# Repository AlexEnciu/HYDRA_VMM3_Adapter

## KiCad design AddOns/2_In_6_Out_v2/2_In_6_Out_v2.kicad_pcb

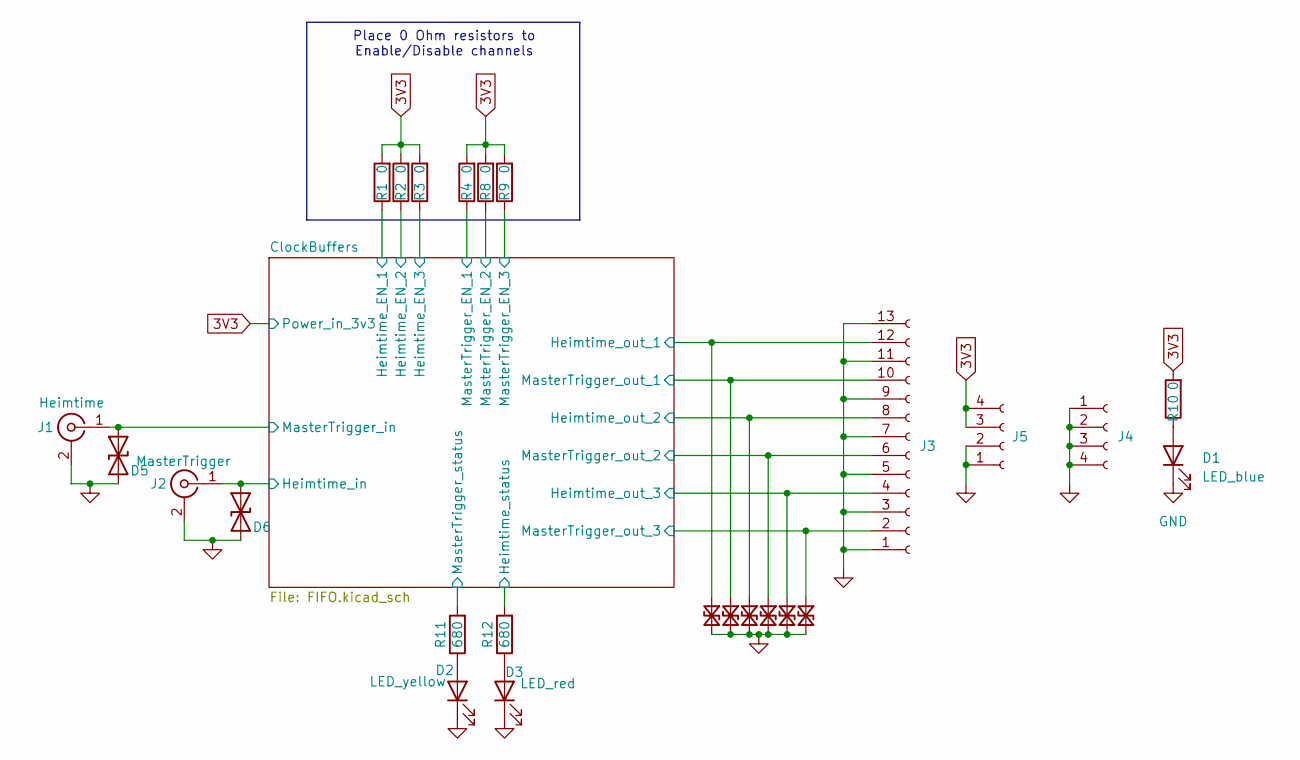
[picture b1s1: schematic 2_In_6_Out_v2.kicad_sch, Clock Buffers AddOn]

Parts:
D1: LED_blue; LED_0603_1608Metric
D2: LED_yellow; LED_0603_1608Metric
D3: LED_red; LED_0603_1608Metric
D5, D6, D7, D8, D9, D10, D11, D13: SP1333-01UTG; D_0201_0603Metric
J1: Heimtime; LINX_CONMCX002-SMD-T
J2: MasterTrigger; LINX_CONMCX002-SMD-T
J3: Conn_01x13_Socket; PinHeader_1x13_P1.27mm_Vertical
J4, J5: Conn_01x04_Socket; PinHeader_1x04_P1.27mm_Vertical
R1, R2, R3, R4, R8, R9: 0; R_0402_1005Metric
R10: 0; R_0603_1608Metric
R11, R12: 680; R_0402_1005Metric

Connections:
3V3: J5.3, J5.4, R1.2, R2.2, R3.2, R4.2, R8.2, R9.2, R10.2; also elsewhere on the board
/ClockBuffers/Heimtime_EN_1: R1.1; also elsewhere on the board
/ClockBuffers/Heimtime_EN_2: R2.1; also elsewhere on the board
/ClockBuffers/Heimtime_EN_3: R3.1; also elsewhere on the board
/ClockBuffers/Heimtime_in: D6.1 (A1), J2.1 (In); also elsewhere on the board
/ClockBuffers/Heimtime_out_1: D13.1 (A1), J3.12; also elsewhere on the board
/ClockBuffers/Heimtime_out_2: D8.1 (A1), J3.8; also elsewhere on the board
/ClockBuffers/Heimtime_out_3: D10.1 (A1), J3.4; also elsewhere on the board
/ClockBuffers/Heimtime_status: R12.2; also elsewhere on the board
/ClockBuffers/MasterTrigger_EN_1: R4.1; also elsewhere on the board
/ClockBuffers/MasterTrigger_EN_2: R8.1; also elsewhere on the board
/ClockBuffers/MasterTrigger_EN_3: R9.1; also elsewhere on the board
/ClockBuffers/MasterTrigger_in: D5.1 (A1), J1.1 (In); also elsewhere on the board
/ClockBuffers/MasterTrigger_out_1: D7.1 (A1), J3.10; also elsewhere on the board
/ClockBuffers/MasterTrigger_out_2: D9.1 (A1), J3.6; also elsewhere on the board
/ClockBuffers/MasterTrigger_out_3: D11.1 (A1), J3.2; also elsewhere on the board
/ClockBuffers/MasterTrigger_status: R11.2; also elsewhere on the board
GND: D1.1 (K), D2.1 (K), D3.1 (K), D5.2 (A2), D6.2 (A2), D7.2 (A2), D8.2 (A2), D9.2 (A2), D10.2 (A2), D11.2 (A2), D13.2 (A2), J1.2 (Ext), J2.2 (Ext), J3.1, J3.3, J3.5, J3.7, J3.9, J3.11, J3.13, J4.1, J4.2, J4.3, J4.4, J5.1, J5.2; also elsewhere on the board
unnamed: D1.2 (A), R10.1
unnamed: D2.2 (A), R11.1
unnamed: D3.2 (A), R12.1

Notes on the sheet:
Place 0 Ohm resistors to Enable/Disable channels

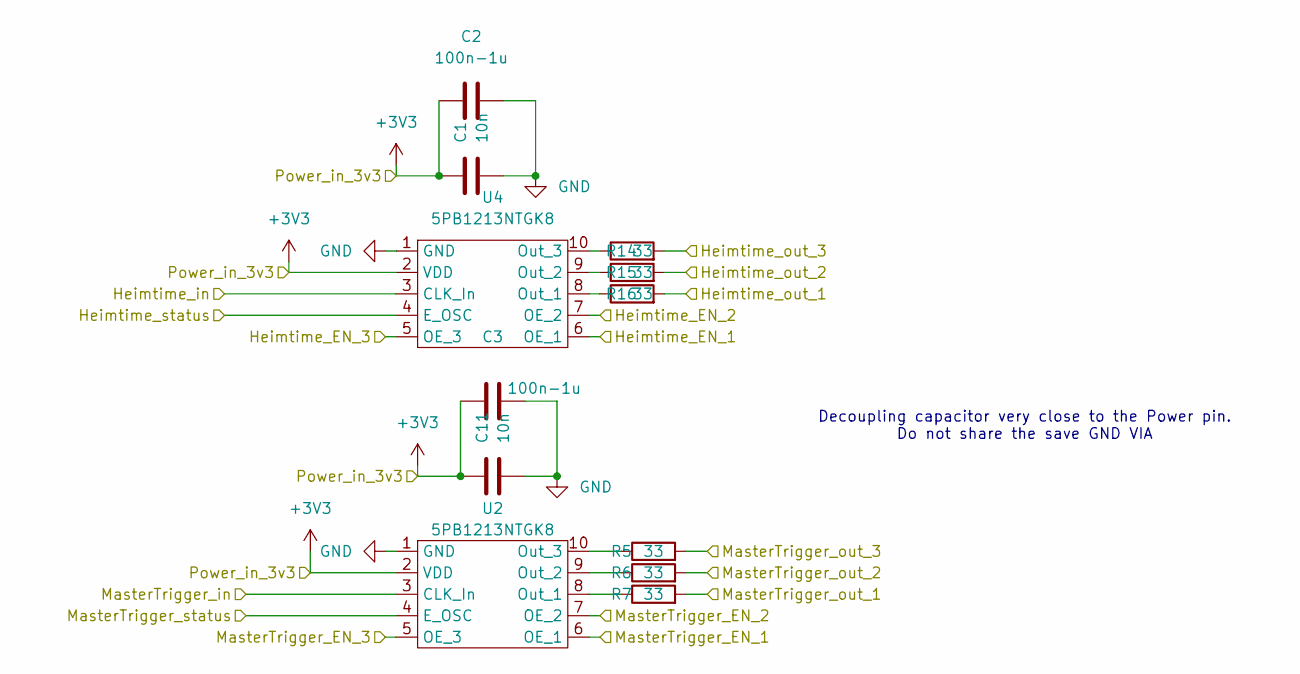
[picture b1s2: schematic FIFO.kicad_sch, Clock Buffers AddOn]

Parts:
C1, C11: 10n; C_0402_1005Metric
C2, C3: 100n-1u; C_0402_1005Metric
R5, R6, R7, R14, R15, R16: 33; R_0402_1005Metric
U2, U4: 5PB1213NTGK8

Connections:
3V3: C1.1, C2.1, C3.1, C11.1, U2.2 (VDD), U4.2 (VDD); also elsewhere on the board
/ClockBuffers/Heimtime_EN_1: U4.6 (OE_1); also elsewhere on the board
/ClockBuffers/Heimtime_EN_2: U4.7 (OE_2); also elsewhere on the board
/ClockBuffers/Heimtime_EN_3: U4.5 (OE_3); also elsewhere on the board
/ClockBuffers/Heimtime_in: U4.3 (CLK_In); also elsewhere on the board
/ClockBuffers/Heimtime_out_1: R16.2; also elsewhere on the board
/ClockBuffers/Heimtime_out_2: R15.2; also elsewhere on the board
/ClockBuffers/Heimtime_out_3: R14.2; also elsewhere on the board
/ClockBuffers/Heimtime_status: U4.4 (E_OSC); also elsewhere on the board
/ClockBuffers/MasterTrigger_EN_1: U2.6 (OE_1); also elsewhere on the board
/ClockBuffers/MasterTrigger_EN_2: U2.7 (OE_2); also elsewhere on the board
/ClockBuffers/MasterTrigger_EN_3: U2.5 (OE_3); also elsewhere on the board
/ClockBuffers/MasterTrigger_in: U2.3 (CLK_In); also elsewhere on the board
/ClockBuffers/MasterTrigger_out_1: R7.2; also elsewhere on the board
/ClockBuffers/MasterTrigger_out_2: R6.2; also elsewhere on the board
/ClockBuffers/MasterTrigger_out_3: R5.2; also elsewhere on the board
/ClockBuffers/MasterTrigger_status: U2.4 (E_OSC); also elsewhere on the board
GND: C1.2, C2.2, C3.2, C11.2, U2.1 (GND), U4.1 (GND); also elsewhere on the board
unnamed: R7.1, U2.8 (Out_1)
unnamed: R6.1, U2.9 (Out_2)
unnamed: R5.1, U2.10 (Out_3)
unnamed: R16.1, U4.8 (Out_1)
unnamed: R15.1, U4.9 (Out_2)
unnamed: R14.1, U4.10 (Out_3)

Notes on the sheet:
Decoupling capacitor very close to the Power pin. Do not share the save GND VIA

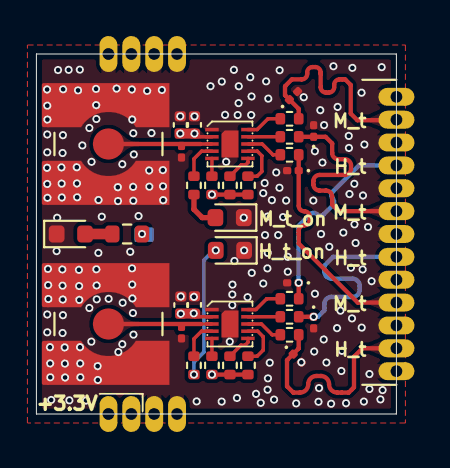
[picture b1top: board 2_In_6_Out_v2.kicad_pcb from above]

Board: 4 copper layers, 20.0 x 20.0 mm, 37 parts (0 on the bottom side), 27 nets.

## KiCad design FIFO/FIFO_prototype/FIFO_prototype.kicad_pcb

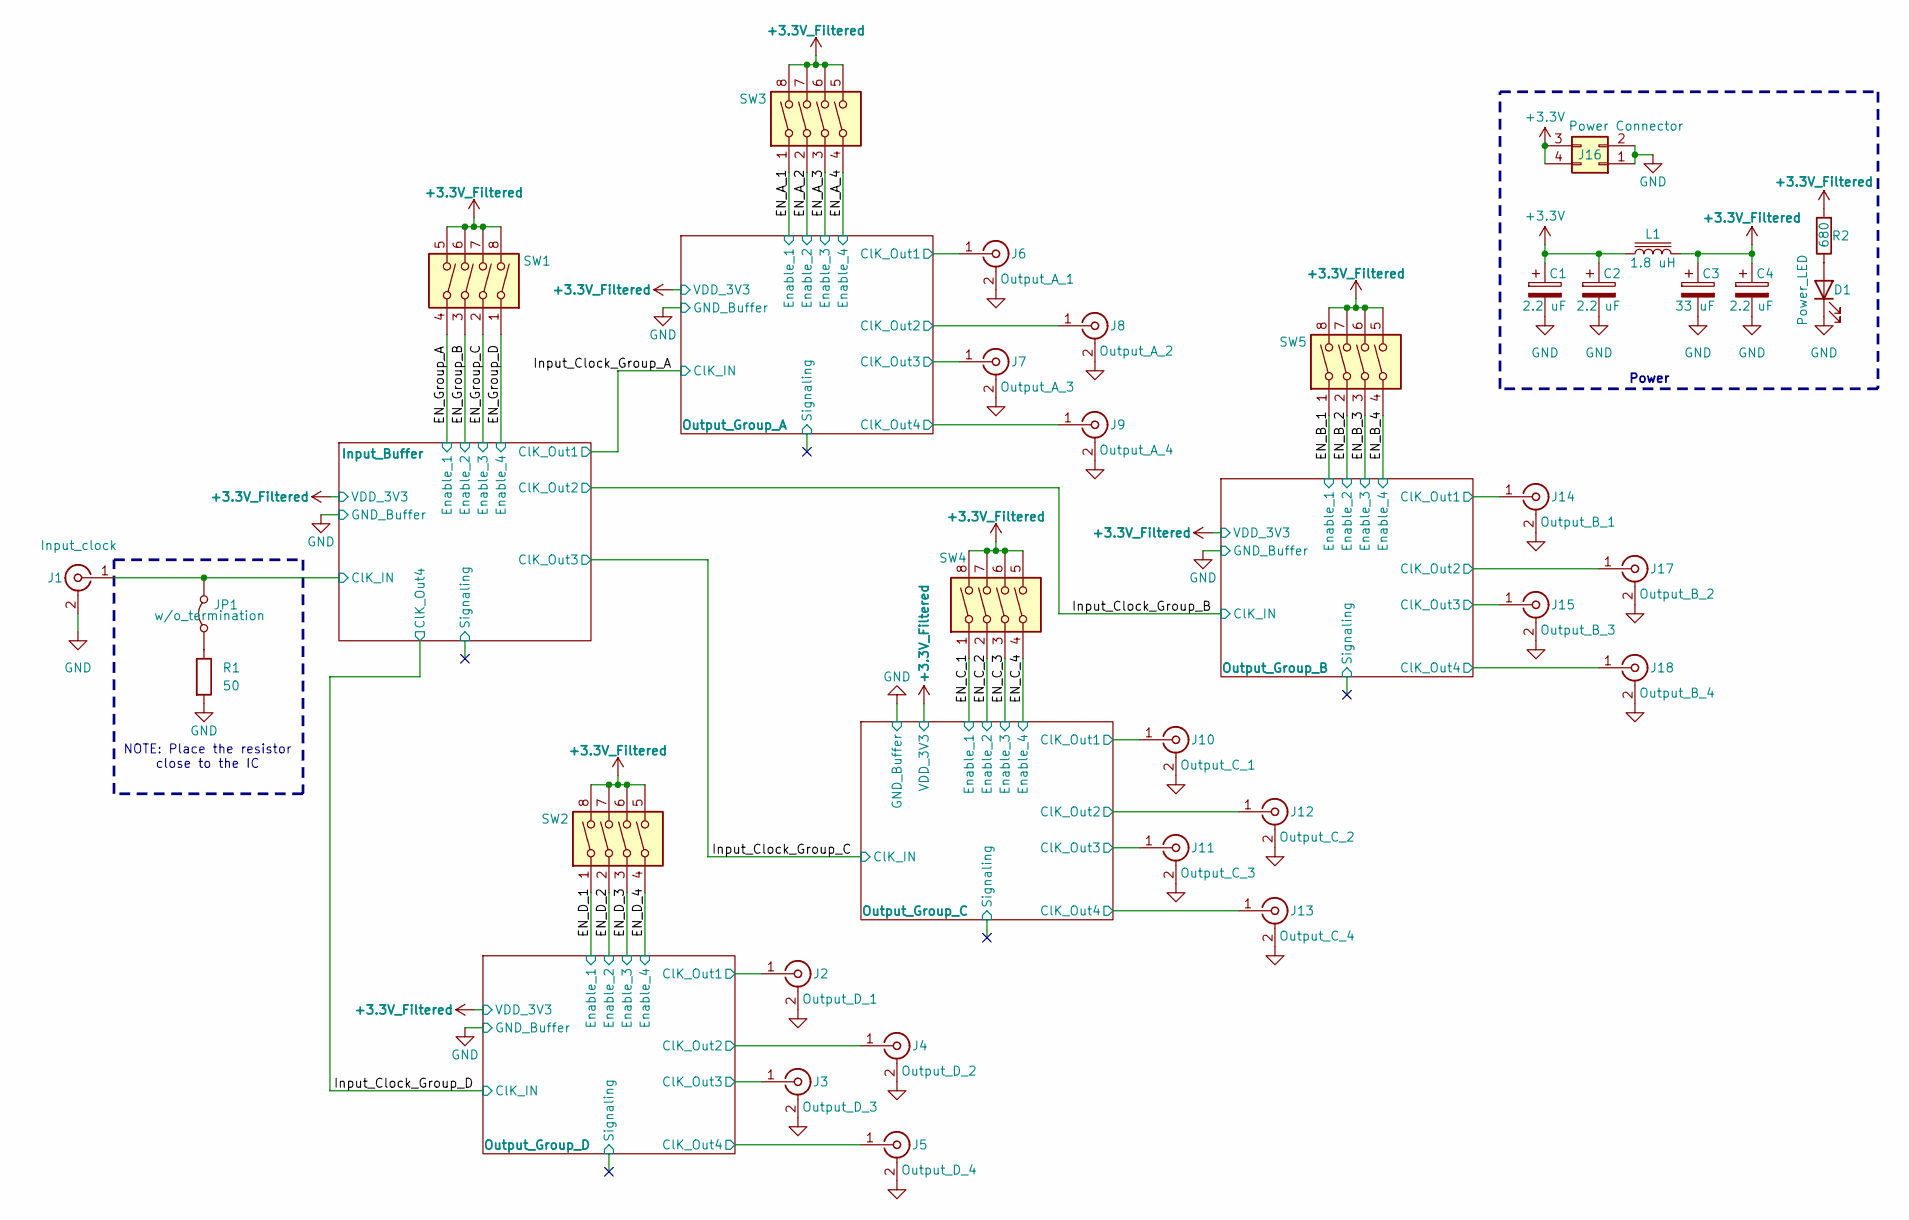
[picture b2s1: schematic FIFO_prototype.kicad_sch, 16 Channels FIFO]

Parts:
C1, C2, C4: 2.2 uF; CP_Elec_4x5.4
C3: 33 uF; CP_EIA-3528-15_AVX-H
D1: Power_LED; LED_0603_1608Metric
J1: Input_clock; SMA_Amphenol_901-143_Horizontal
J2: Output_D_1; SMA_Amphenol_901-143_Horizontal
J3: Output_D_3; SMA_Amphenol_901-143_Horizontal
J4: Output_D_2; SMA_Amphenol_901-143_Horizontal
J5: Output_D_4; SMA_Amphenol_901-143_Horizontal
J6: Output_A_1; SMA_Amphenol_901-143_Horizontal
J7: Output_A_3; SMA_Amphenol_901-143_Horizontal
J8: Output_A_2; SMA_Amphenol_901-143_Horizontal
J9: Output_A_4; SMA_Amphenol_901-143_Horizontal
J10: Output_C_1; SMA_Amphenol_901-143_Horizontal
J11: Output_C_3; SMA_Amphenol_901-143_Horizontal
J12: Output_C_2; SMA_Amphenol_901-143_Horizontal
J13: Output_C_4; SMA_Amphenol_901-143_Horizontal
J14: Output_B_1; SMA_Amphenol_901-143_Horizontal
J15: Output_B_3; SMA_Amphenol_901-143_Horizontal
J16: Power Connector; SAMTEC_IPL1-102-01-X-D-RA-K
J17: Output_B_2; SMA_Amphenol_901-143_Horizontal
J18: Output_B_4; SMA_Amphenol_901-143_Horizontal
JP1: w/o_termination; PinHeader_2x01_P2.54mm_Vertical_SMD
L1: 1.8 uH; WE-TPC_4828; PartNumber 7440430018
R1: 50; R_0201_0603Metric
R2: 680; R_0201_0603Metric
SW1, SW2, SW3, SW4, SW5: SW_DIP_x04; SW_DIP_SPSTx04_Slide_6.7x11.72mm_W6.73mm_P2.54mm_LowProfile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

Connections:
+3.3V: C1.1, C2.1, J16.3, J16.4, L1.1
+3.3V_Filtered: C3.1, C4.1, L1.2, R2.2, SW1.5, SW1.6, SW1.7, SW1.8, SW2.5, SW2.6, SW2.7, SW2.8, SW3.5, SW3.6, SW3.7, SW3.8, SW4.5, SW4.6, SW4.7, SW4.8, SW5.5, SW5.6, SW5.7, SW5.8; also elsewhere on the board
/EN_A_1: SW3.4; also elsewhere on the board
/EN_A_2: SW3.3; also elsewhere on the board
/EN_A_3: SW3.2; also elsewhere on the board
/EN_A_4: SW3.1; also elsewhere on the board
/EN_B_1: SW5.4; also elsewhere on the board
/EN_B_2: SW5.3; also elsewhere on the board
/EN_B_3: SW5.2; also elsewhere on the board
/EN_B_4: SW5.1; also elsewhere on the board
/EN_C_1: SW4.4; also elsewhere on the board
/EN_C_2: SW4.3; also elsewhere on the board
/EN_C_3: SW4.2; also elsewhere on the board
/EN_C_4: SW4.1; also elsewhere on the board
/EN_D_1: SW2.4; also elsewhere on the board
/EN_D_2: SW2.3; also elsewhere on the board
/EN_D_3: SW2.2; also elsewhere on the board
/EN_D_4: SW2.1; also elsewhere on the board
/EN_Group_A: SW1.4; also elsewhere on the board
/EN_Group_B: SW1.3; also elsewhere on the board
/EN_Group_C: SW1.2; also elsewhere on the board
/EN_Group_D: SW1.1; also elsewhere on the board
/Input_Buffer/ClK_IN: J1.1 (In), JP1.2 (B); also elsewhere on the board
/Output_Group_A/ClK_Out1: J6.1 (In); also elsewhere on the board
/Output_Group_A/ClK_Out2: J8.1 (In); also elsewhere on the board
/Output_Group_A/ClK_Out3: J7.1 (In); also elsewhere on the board
/Output_Group_A/ClK_Out4: J9.1 (In); also elsewhere on the board
/Output_Group_B/ClK_Out1: J14.1 (In); also elsewhere on the board
/Output_Group_B/ClK_Out2: J17.1 (In); also elsewhere on the board
/Output_Group_B/ClK_Out3: J15.1 (In); also elsewhere on the board
/Output_Group_B/ClK_Out4: J18.1 (In); also elsewhere on the board
/Output_Group_C/ClK_Out1: J10.1 (In); also elsewhere on the board
/Output_Group_C/ClK_Out2: J12.1 (In); also elsewhere on the board
/Output_Group_C/ClK_Out3: J11.1 (In); also elsewhere on the board
/Output_Group_C/ClK_Out4: J13.1 (In); also elsewhere on the board
/Output_Group_D/ClK_Out1: J2.1 (In); also elsewhere on the board
/Output_Group_D/ClK_Out2: J4.1 (In); also elsewhere on the board
/Output_Group_D/ClK_Out3: J3.1 (In); also elsewhere on the board
/Output_Group_D/ClK_Out4: J5.1 (In); also elsewhere on the board
GND: C1.2, C2.2, C3.2, C4.2, D1.1 (K), J1.2 (Ext), J2.2 (Ext), J3.2 (Ext), J4.2 (Ext), J5.2 (Ext), J6.2 (Ext), J7.2 (Ext), J8.2 (Ext), J9.2 (Ext), J10.2 (Ext), J11.2 (Ext), J12.2 (Ext), J13.2 (Ext), J14.2 (Ext), J15.2 (Ext), J16.1, J16.2, J17.2 (Ext), J18.2 (Ext), R1.2; also elsewhere on the board
unnamed: D1.2 (A), R2.1
unnamed: JP1.1 (A), R1.1

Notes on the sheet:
NOTE: Place the resistor close to the IC
Power

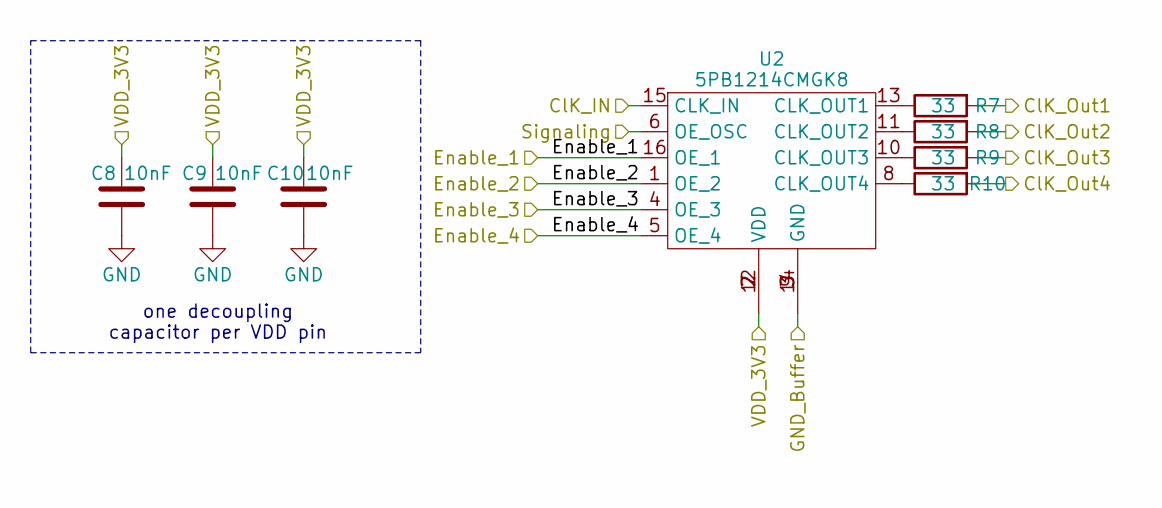
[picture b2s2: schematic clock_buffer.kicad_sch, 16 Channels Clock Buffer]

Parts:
C8, C9, C10: 10nF; C_0201_0603Metric
R7, R8, R9, R10: 33; R_0201_0603Metric
U2: 5PB1214CMGK8

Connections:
+3.3V_Filtered: C8.2, C9.2, C10.2, U2.2 (VDD), U2.7 (VDD), U2.12 (VDD); also elsewhere on the board
/EN_A_1: U2.16 (OE_1); also elsewhere on the board
/EN_A_2: U2.1 (OE_2); also elsewhere on the board
/EN_A_3: U2.4 (OE_3); also elsewhere on the board
/EN_A_4: U2.5 (OE_4); also elsewhere on the board
/Input_Clock_Group_A: U2.15 (CLK_IN); also elsewhere on the board
/Output_Group_A/ClK_Out1: R7.2; also elsewhere on the board
/Output_Group_A/ClK_Out2: R8.2; also elsewhere on the board
/Output_Group_A/ClK_Out3: R9.2; also elsewhere on the board
/Output_Group_A/ClK_Out4: R10.2; also elsewhere on the board
/Output_Group_A/Signaling: U2.6 (OE_OSC)
GND: C8.1, C9.1, C10.1, U2.3 (GND), U2.9 (GND), U2.14 (GND); also elsewhere on the board
unnamed: R7.1, U2.13 (CLK_OUT1)
unnamed: R8.1, U2.11 (CLK_OUT2)
unnamed: R9.1, U2.10 (CLK_OUT3)
unnamed: R10.1, U2.8 (CLK_OUT4)

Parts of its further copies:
C5, C6, C7, C11, C12, C13, C14, C15, C16, C17, C18, C19: 10nF; C_0201_0603Metric
R3, R4, R5, R6, R11, R12, R13, R14, R15, R16, R17, R18, R19, R20, R21, R22: 33; R_0201_0603Metric
U1, U3, U4, U5: 5PB1214CMGK8

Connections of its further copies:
+3.3V_Filtered: C5.2, C6.2, C7.2, C11.2, C12.2, C13.2, C14.2, C15.2, C16.2, C17.2, C18.2, C19.2, U1.2 (VDD), U1.7 (VDD), U1.12 (VDD), U3.2 (VDD), U3.7 (VDD), U3.12 (VDD), U4.2 (VDD), U4.7 (VDD), U4.12 (VDD), U5.2 (VDD), U5.7 (VDD), U5.12 (VDD); also elsewhere on the board
/EN_B_1: U3.16 (OE_1); also elsewhere on the board
/EN_B_2: U3.1 (OE_2); also elsewhere on the board
/EN_B_3: U3.4 (OE_3); also elsewhere on the board
/EN_B_4: U3.5 (OE_4); also elsewhere on the board
/EN_C_1: U4.16 (OE_1); also elsewhere on the board
/EN_C_2: U4.1 (OE_2); also elsewhere on the board
/EN_C_3: U4.4 (OE_3); also elsewhere on the board
/EN_C_4: U4.5 (OE_4); also elsewhere on the board
/EN_D_1: U5.16 (OE_1); also elsewhere on the board
/EN_D_2: U5.1 (OE_2); also elsewhere on the board
/EN_D_3: U5.4 (OE_3); also elsewhere on the board
/EN_D_4: U5.5 (OE_4); also elsewhere on the board
/EN_Group_A: U1.16 (OE_1); also elsewhere on the board
/EN_Group_B: U1.1 (OE_2); also elsewhere on the board
/EN_Group_C: U1.4 (OE_3); also elsewhere on the board
/EN_Group_D: U1.5 (OE_4); also elsewhere on the board
/Input_Buffer/ClK_IN: U1.15 (CLK_IN); also elsewhere on the board
/Input_Buffer/Signaling: U1.6 (OE_OSC)
/Input_Clock_Group_A: R3.2; also elsewhere on the board
/Input_Clock_Group_B: R4.2, U3.15 (CLK_IN)
/Input_Clock_Group_C: R5.2, U4.15 (CLK_IN)
/Input_Clock_Group_D: R6.2, U5.15 (CLK_IN)
/Output_Group_B/ClK_Out1: R11.2; also elsewhere on the board
/Output_Group_B/ClK_Out2: R12.2; also elsewhere on the board
/Output_Group_B/ClK_Out3: R13.2; also elsewhere on the board
/Output_Group_B/ClK_Out4: R14.2; also elsewhere on the board
/Output_Group_B/Signaling: U3.6 (OE_OSC)
/Output_Group_C/ClK_Out1: R15.2; also elsewhere on the board
/Output_Group_C/ClK_Out2: R16.2; also elsewhere on the board
/Output_Group_C/ClK_Out3: R17.2; also elsewhere on the board
/Output_Group_C/ClK_Out4: R18.2; also elsewhere on the board
/Output_Group_C/Signaling: U4.6 (OE_OSC)
/Output_Group_D/ClK_Out1: R19.2; also elsewhere on the board
/Output_Group_D/ClK_Out2: R20.2; also elsewhere on the board
/Output_Group_D/ClK_Out3: R21.2; also elsewhere on the board
/Output_Group_D/ClK_Out4: R22.2; also elsewhere on the board
/Output_Group_D/Signaling: U5.6 (OE_OSC)
GND: C5.1, C6.1, C7.1, C11.1, C12.1, C13.1, C14.1, C15.1, C16.1, C17.1, C18.1, C19.1, U1.3 (GND), U1.9 (GND), U1.14 (GND), U3.3 (GND), U3.9 (GND), U3.14 (GND), U4.3 (GND), U4.9 (GND), U4.14 (GND), U5.3 (GND), U5.9 (GND), U5.14 (GND); also elsewhere on the board
unnamed: R3.1, U1.13 (CLK_OUT1)
unnamed: R4.1, U1.11 (CLK_OUT2)
unnamed: R5.1, U1.10 (CLK_OUT3)
unnamed: R6.1, U1.8 (CLK_OUT4)
unnamed: R11.1, U3.13 (CLK_OUT1)
unnamed: R12.1, U3.11 (CLK_OUT2)
unnamed: R13.1, U3.10 (CLK_OUT3)
unnamed: R14.1, U3.8 (CLK_OUT4)
unnamed: R15.1, U4.13 (CLK_OUT1)
unnamed: R16.1, U4.11 (CLK_OUT2)
unnamed: R17.1, U4.10 (CLK_OUT3)
unnamed: R18.1, U4.8 (CLK_OUT4)
unnamed: R19.1, U5.13 (CLK_OUT1)
unnamed: R20.1, U5.11 (CLK_OUT2)
unnamed: R21.1, U5.10 (CLK_OUT3)
unnamed: R22.1, U5.8 (CLK_OUT4)

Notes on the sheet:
one decoupling capacitor per VDD pin

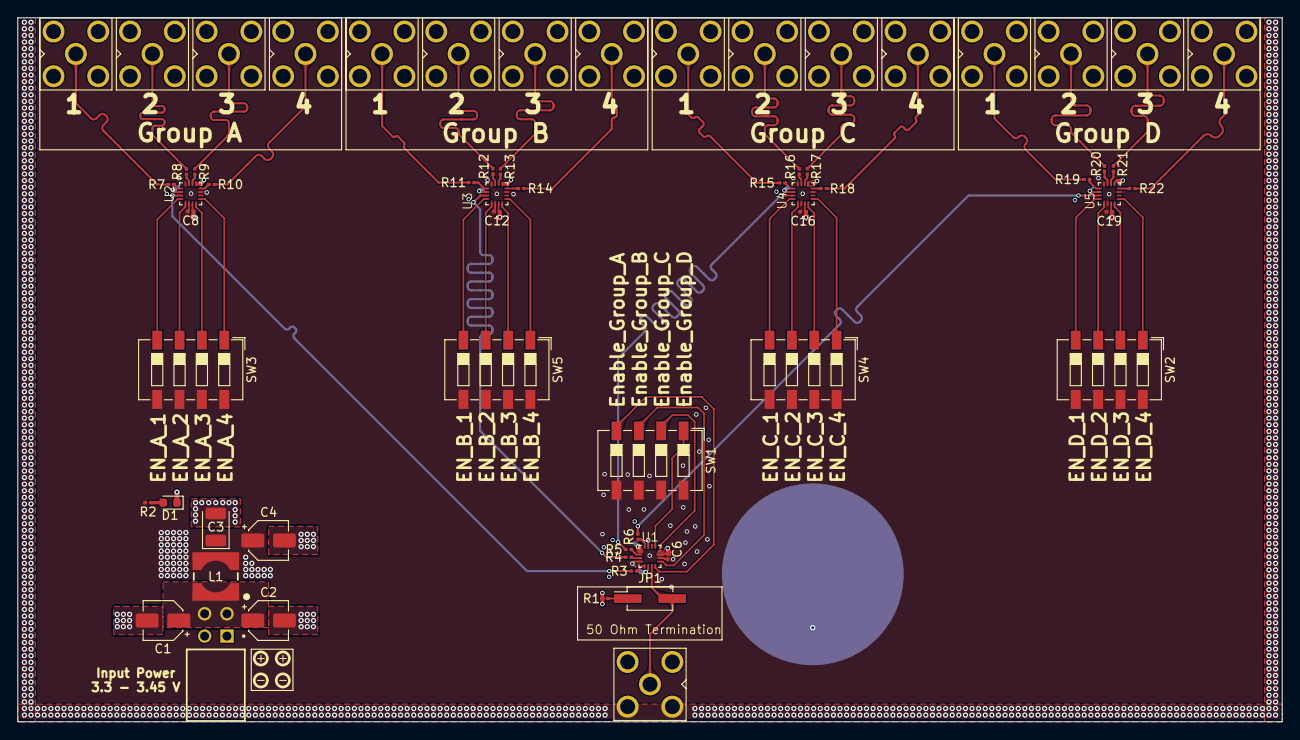
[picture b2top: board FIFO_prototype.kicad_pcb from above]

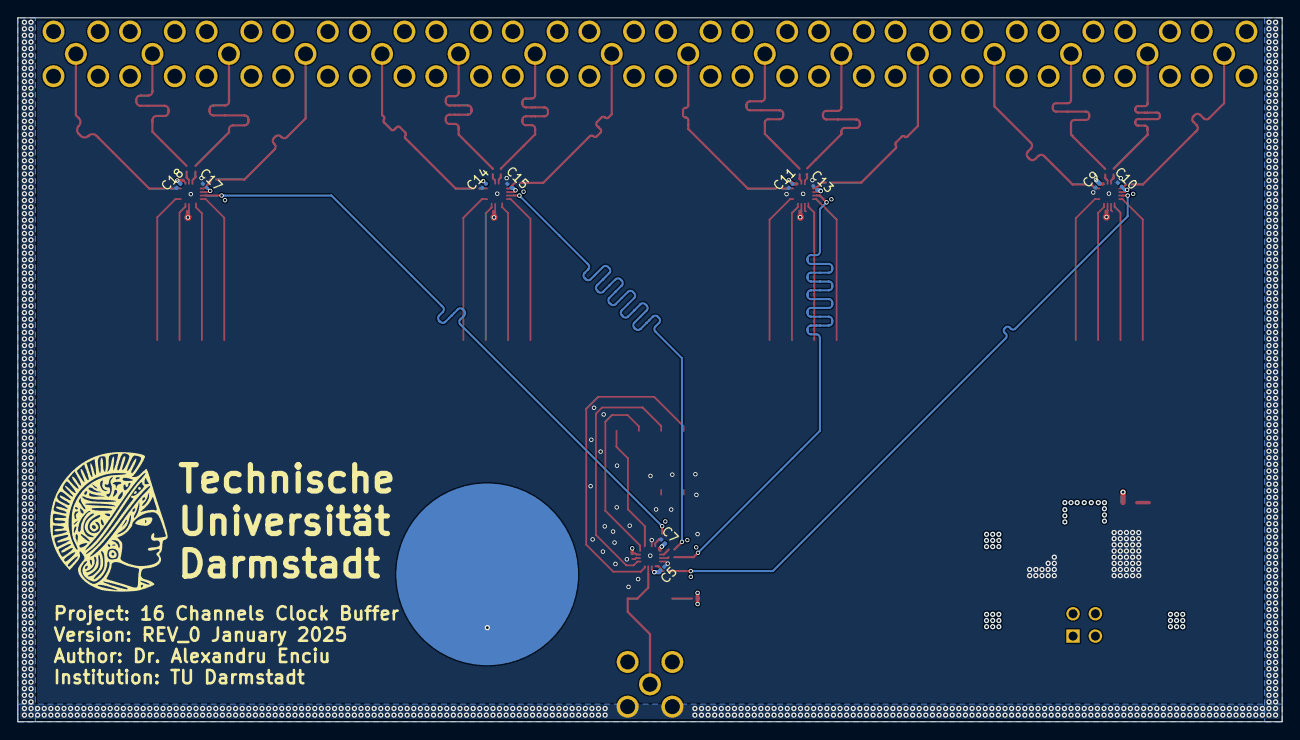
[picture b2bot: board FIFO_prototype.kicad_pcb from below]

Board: 4 copper layers, 143.7 x 80.0 mm, 72 parts (10 on the bottom side), 66 nets.
